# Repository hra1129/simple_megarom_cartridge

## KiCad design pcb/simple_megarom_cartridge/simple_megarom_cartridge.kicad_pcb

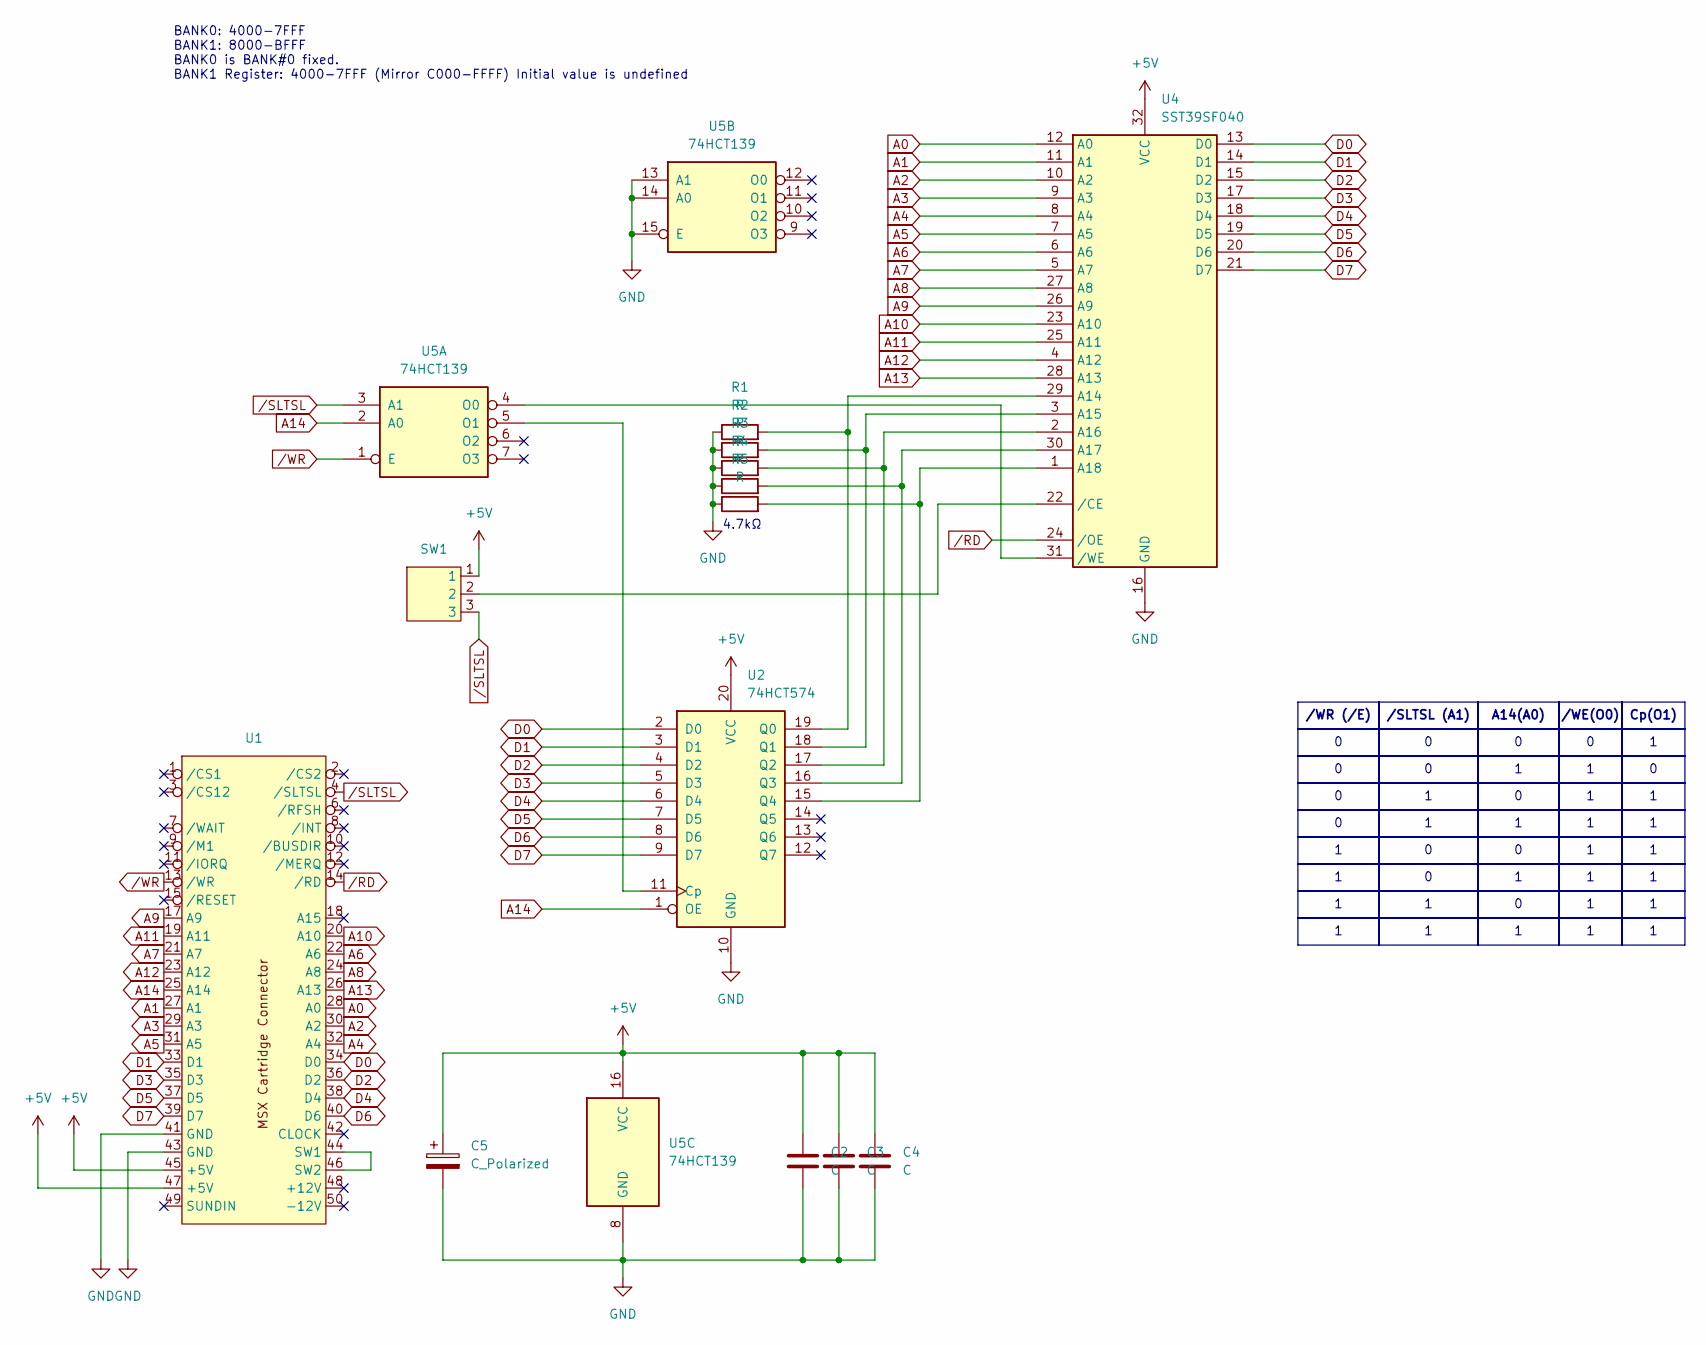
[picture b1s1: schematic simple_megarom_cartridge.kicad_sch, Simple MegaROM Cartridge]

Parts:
C2, C3, C4: C; C_Disc_D5.0mm_W2.5mm_P5.00mm
C5: C_Polarized; CP_Radial_D5.0mm_P2.50mm
R1, R2, R3, R4, R5: R; R_Axial_DIN0204_L3.6mm_D1.6mm_P5.08mm_Horizontal
SW1: PinHeader_1x03_P2.54mm_Vertical
U1: MSX Cartridge_1
U2: 74HCT574; DIP-20_W7.62mm
U4: SST39SF040; DIP-32_W15.24mm
U5: 74HCT139; DIP-16_W7.62mm

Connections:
+5V: C2.1, C3.1, C4.1, C5.1, SW1.1, U1.45 (+5V), U1.47 (+5V), U2.20 (VCC), U4.32 (VCC), U5.16 (VCC)
A0: U1.28 (A0), U4.12 (A0)
A1: U1.27 (A1), U4.11 (A1)
A2: U1.30 (A2), U4.10 (A2)
A3: U1.29 (A3), U4.9 (A3)
A4: U1.32 (A4), U4.8 (A4)
A5: U1.31 (A5), U4.7 (A5)
A6: U1.22 (A6), U4.6 (A6)
A7: U1.21 (A7), U4.5 (A7)
A8: U1.24 (A8), U4.27 (A8)
A9: U1.17 (A9), U4.26 (A9)
A10: U1.20 (A10), U4.23 (A10)
A11: U1.19 (A11), U4.25 (A11)
A12: U1.23 (A12), U4.4 (A12)
A13: U1.26 (A13), U4.28 (A13)
A14: U1.25 (A14), U2.1 (OE), U5.2 (A0)
D0: U1.34 (D0), U2.2 (D0), U4.13 (D0)
D1: U1.33 (D1), U2.3 (D1), U4.14 (D1)
D2: U1.36 (D2), U2.4 (D2), U4.15 (D2)
D3: U1.35 (D3), U2.5 (D3), U4.17 (D3)
D4: U1.38 (D4), U2.6 (D4), U4.18 (D4)
D5: U1.37 (D5), U2.7 (D5), U4.19 (D5)
D6: U1.40 (D6), U2.8 (D6), U4.20 (D6)
D7: U1.39 (D7), U2.9 (D7), U4.21 (D7)
GND: C2.2, C3.2, C4.2, C5.2, R1.1, R2.1, R3.1, R4.1, R5.1, U1.41 (GND), U1.43 (GND), U2.10 (GND), U4.16 (GND), U5.8 (GND), U5.13 (A1), U5.14 (A0), U5.15 (E)
unnamed: U1.44 (SW1), U1.46 (SW2)
unnamed: U2.11 (Cp), U5.5 (O1)
unnamed: R1.2, U2.19 (Q0), U4.29 (A14)
unnamed: R2.2, U2.18 (Q1), U4.3 (A15)
unnamed: R3.2, U2.17 (Q2), U4.2 (A16)
unnamed: R4.2, U2.16 (Q3), U4.30 (A17)
unnamed: R5.2, U2.15 (Q4), U4.1 (A18)
unnamed: SW1.2, U4.22 (/CE)
unnamed: U4.31 (/WE), U5.4 (O0)
/RD: U1.14 (/RD), U4.24 (/OE)
/SLTSL: SW1.3, U1.4 (/SLTSL), U5.3 (A1)
/WR: U1.13 (/WR), U5.1 (E)

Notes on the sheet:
/WR (/E)
/SLTSL (A1)
A14(A0)
Cp(O1)
/WE(O0)
BANK0: 4000-7FFF BANK1: 8000-BFFF BANK0 is BANK#0 fixed. BANK1 Register: 4000-7FFF (Mirror C000-FFFF) Initial value is undefined
4.7kΩ

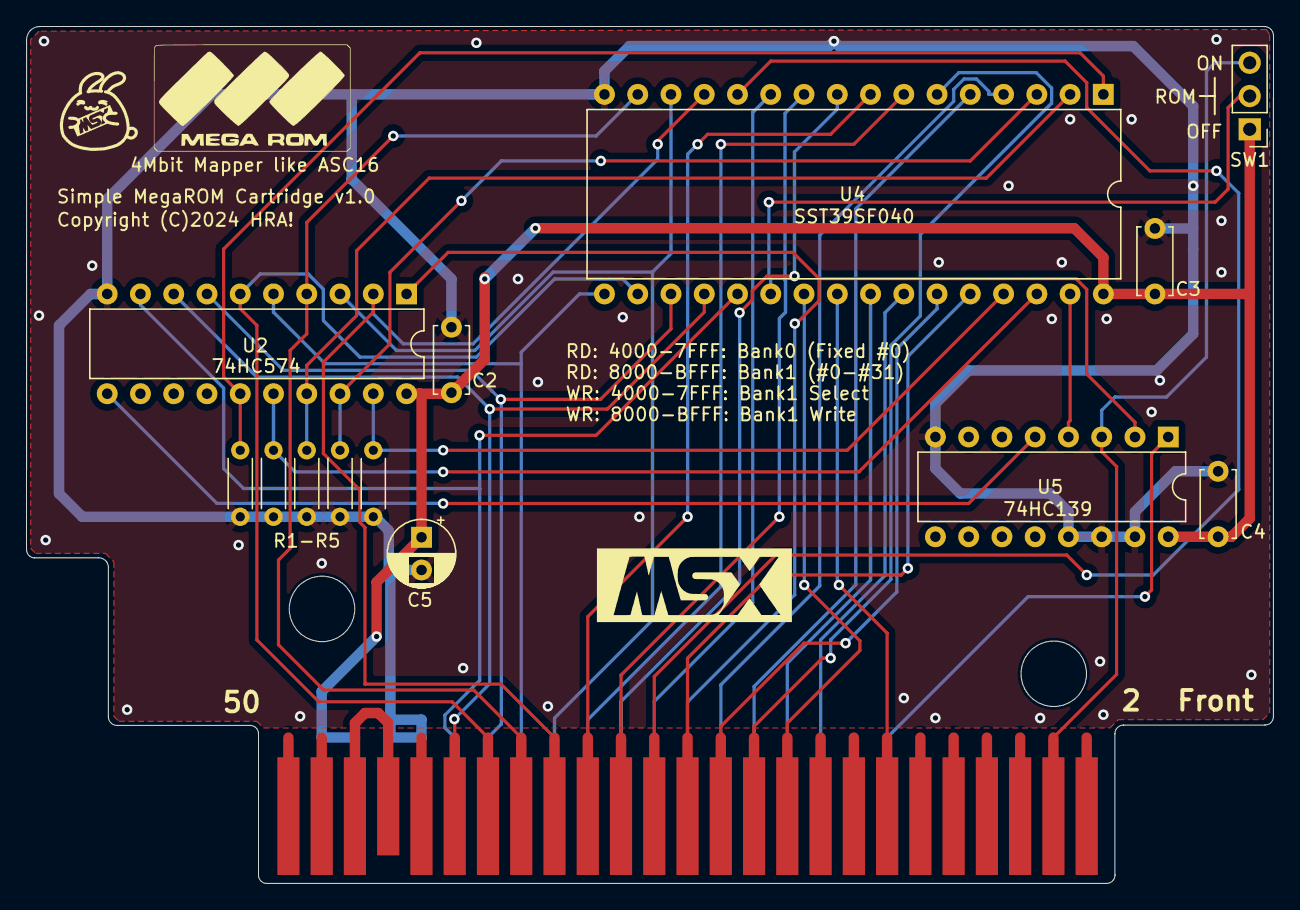
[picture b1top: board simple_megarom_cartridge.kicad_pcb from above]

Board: 2 copper layers, 95.2 x 65.4 mm, 14 parts (0 on the bottom side), 37 nets.

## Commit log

2024-06-21 Added documents
2024-06-22 Updated simple_megarom_cartridge.pdf
    資料に追記

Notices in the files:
pcb/simple_megarom_cartridge/simple_megarom_cartridge.kicad_pcb:
Copyright (C)2024 HRA!
